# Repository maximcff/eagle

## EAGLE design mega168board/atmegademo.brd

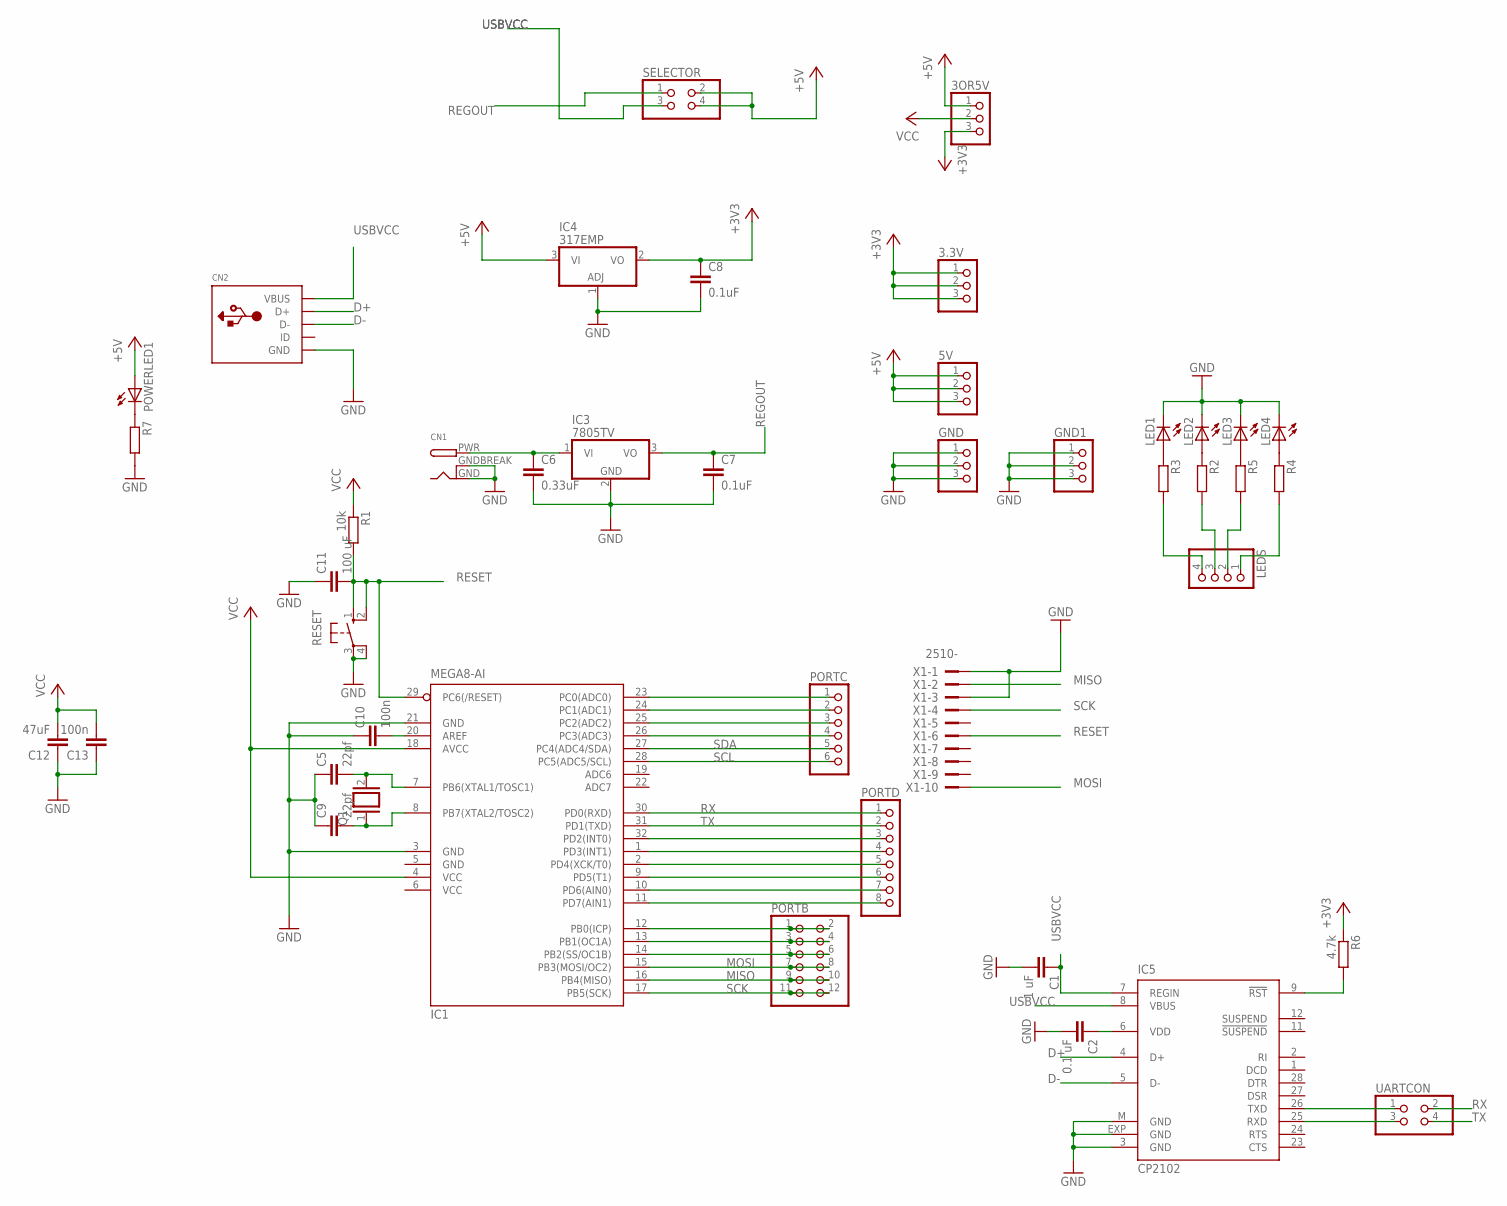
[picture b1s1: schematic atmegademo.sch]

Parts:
3.3V, 3OR5V, 5V: PINHD-1X3; 1X03
C1: 1 uF; C0805K
C2: 0.1 uF; C0805K
C5, C9: 22pf; C0805K
C6: 0.33uF; C0805K
C7, C8: 0.1uF; C0805K
C10, C13: 100n; C0805K
C11: 100 uF; C0805K
C12: 47uF; C0805K
CN1: DCBARRELPTH; DCJACK_2MM_PTH
CN2: USBMINIB; USB-MINIB
GND, GND1: PINHD-1X3; 1X03
IC1: MEGA8-AI; TQFP32-08
IC3: 7805TV; TO220V
IC4: 317EMP; SOT223
IC5: CP2102; MLP28
LED1, LED2, LED3, LED4: LEDCHIPLED_1206; CHIPLED_1206
LEDS: PINHD-1X4; 1X04
PORTB: PINHD-2X6; 2X06
PORTC: PINHD-1X6CLEAN; 1X06-CLEAN
PORTD: PINHD-1X8CLEANBIG; 1X08-CLEANBIG
POWERLED1: LEDCHIPLED_1206; CHIPLED_1206
Q1: XTAL/S; QS
R1: 10k; 0207/12
R2, R3, R4, R5, R7: R-EU_R0805; R0805
R6: 4.7k; R0805
RESET: 10-XX; B3F-10XX
SELECTOR: PINHD-2X2; 2X02
UARTCON: PINHD-2X2; 2X02
X1: 2510-; PAK100/2500-10

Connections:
+3V3: 3.3V.1, 3.3V.2, 3.3V.3, 3OR5V.3, C8.1, IC4.2 (VO), R6.1
+5V: 3OR5V.1, 5V.1, 5V.2, 5V.3, IC4.3 (VI), POWERLED1.A, SELECTOR.2, SELECTOR.4
D+: CN2.D+, IC5.4 (D+)
D-: CN2.D-, IC5.5 (D-)
GND: C1.2, C2.2, C5.1, C6.2, C7.2, C8.2, C9.1, C10.1, C11.1, C12.1, C13.1, CN1.GND, CN1.GNDBREAK, CN2.GND, GND.1, GND.2, GND.3, GND1.1, GND1.2, GND1.3, IC1.3 (GND), IC1.5 (GND), IC1.21 (GND), IC3.2 (GND), IC4.1 (ADJ), IC5.3 (GND), IC5.EXP (GND), IC5.M (GND), LED1.C, LED2.C, LED3.C, LED4.C, R7.2, RESET.3, RESET.4 (P1), X1.1, X1.3
MISO: IC1.16 (PB4(MISO)), PORTB.9, PORTB.10, X1.2
MOSI: IC1.15 (PB3(MOSI/OC2)), PORTB.7, PORTB.8, X1.10
unnamed: IC5.26 (TXD), UARTCON.1
unnamed: POWERLED1.C, R7.1
unnamed: C2.1, IC5.6 (VDD)
unnamed: IC5.9 (!RST), R6.2
unnamed: IC5.25 (RXD), UARTCON.3
unnamed: LEDS.4, R3.2
unnamed: LEDS.3, R2.2
unnamed: IC1.32 (PD2(INT0)), PORTD.3
unnamed: IC1.1 (PD3(INT1)), PORTD.4
unnamed: IC1.2 (PD4(XCK/T0)), PORTD.5
unnamed: C6.1, CN1.PWR, IC3.1 (VI)
unnamed: IC1.9 (PD5(T1)), PORTD.6
unnamed: IC1.23 (PC0(ADC0)), PORTC.1
unnamed: IC1.10 (PD6(AIN0)), PORTD.7
unnamed: IC1.11 (PD7(AIN1)), PORTD.8
unnamed: IC1.24 (PC1(ADC1)), PORTC.2
unnamed: IC1.25 (PC2(ADC2)), PORTC.3
unnamed: IC1.26 (PC3(ADC3)), PORTC.4
unnamed: LEDS.2, R5.2
unnamed: LED1.A, R3.1
unnamed: LED2.A, R2.1
unnamed: C10.2, IC1.20 (AREF)
unnamed: C5.2, IC1.7 (PB6(XTAL1/TOSC1)), Q1.2
unnamed: LED4.A, R4.1
unnamed: LED3.A, R5.1
unnamed: C9.2, IC1.8 (PB7(XTAL2/TOSC2)), Q1.1
unnamed: IC1.13 (PB1(OC1A)), PORTB.3, PORTB.4
unnamed: IC1.14 (PB2(SS/OC1B)), PORTB.5, PORTB.6
unnamed: IC1.12 (PB0(ICP)), PORTB.1, PORTB.2
unnamed: LEDS.1, R4.2
REGOUT: C7.1, IC3.3 (VO), SELECTOR.1
RESET: C11.2, IC1.29 (PC6(/RESET)), R1.2, RESET.1 (S), RESET.2 (S1), X1.6
RX: IC1.30 (PD0(RXD)), PORTD.1, UARTCON.2
SCK: IC1.17 (PB5(SCK)), PORTB.11, PORTB.12, X1.4
SCL: IC1.28 (PC5(ADC5/SCL)), PORTC.6
SDA: IC1.27 (PC4(ADC4/SDA)), PORTC.5
TX: IC1.31 (PD1(TXD)), PORTD.2, UARTCON.4
USBVCC: C1.1, CN2.VBUS, IC5.7 (REGIN), IC5.8 (VBUS), SELECTOR.3
VCC: 3OR5V.2, C12.2, C13.2, IC1.4 (VCC), IC1.6 (VCC), IC1.18 (AVCC), R1.1

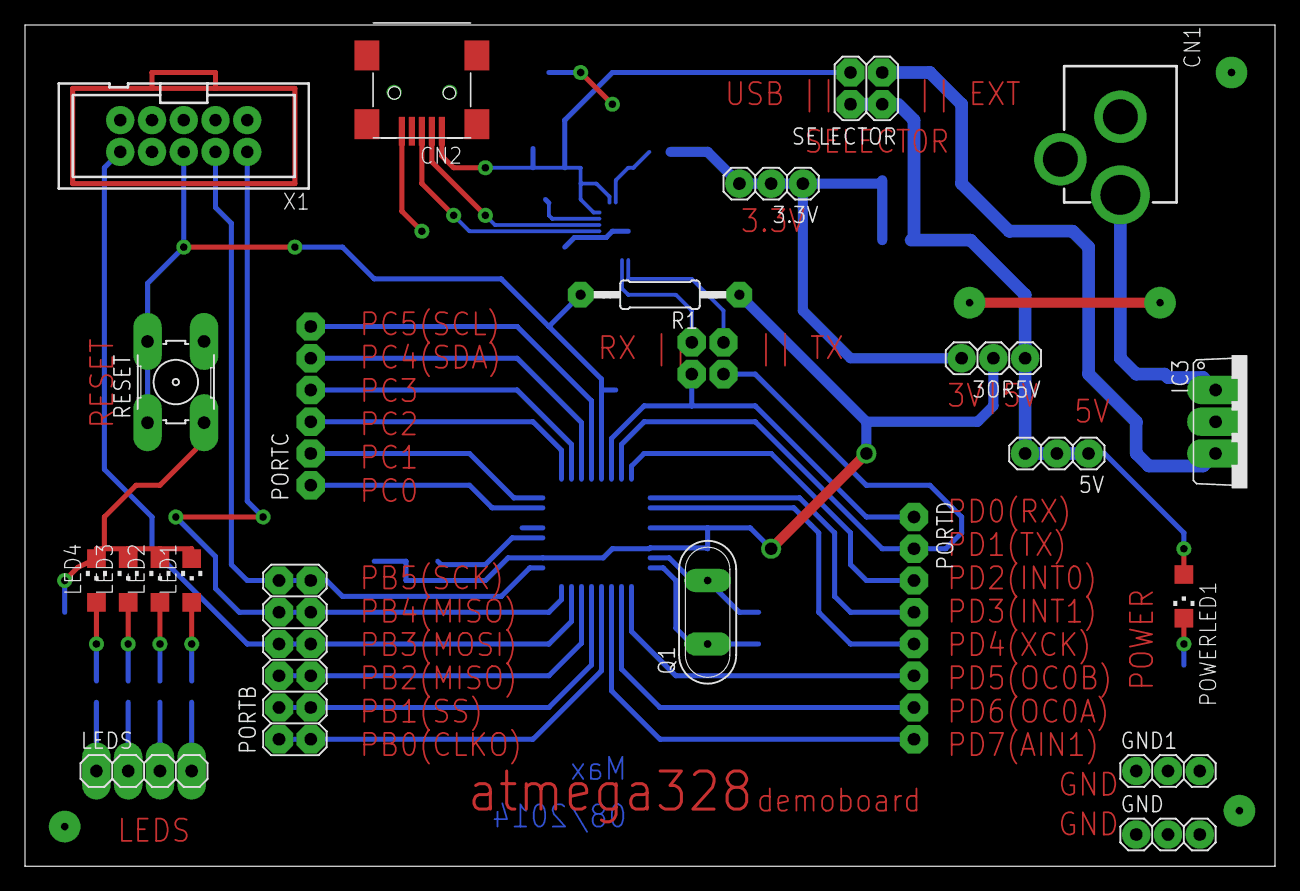
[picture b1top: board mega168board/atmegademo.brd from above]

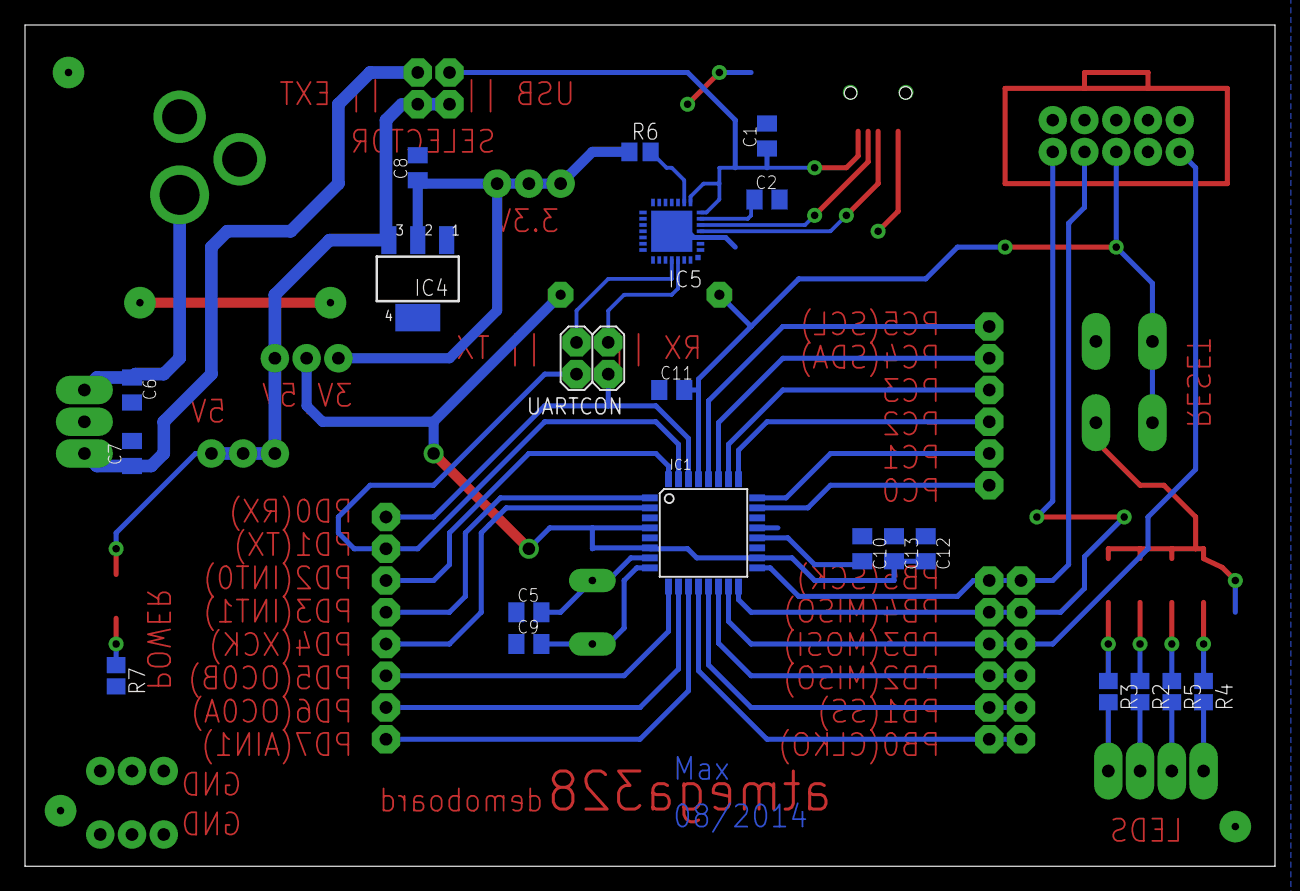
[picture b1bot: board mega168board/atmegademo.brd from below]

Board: 2 copper layers, 100.0 x 67.3 mm, 43 parts (21 on the bottom side), 46 nets.

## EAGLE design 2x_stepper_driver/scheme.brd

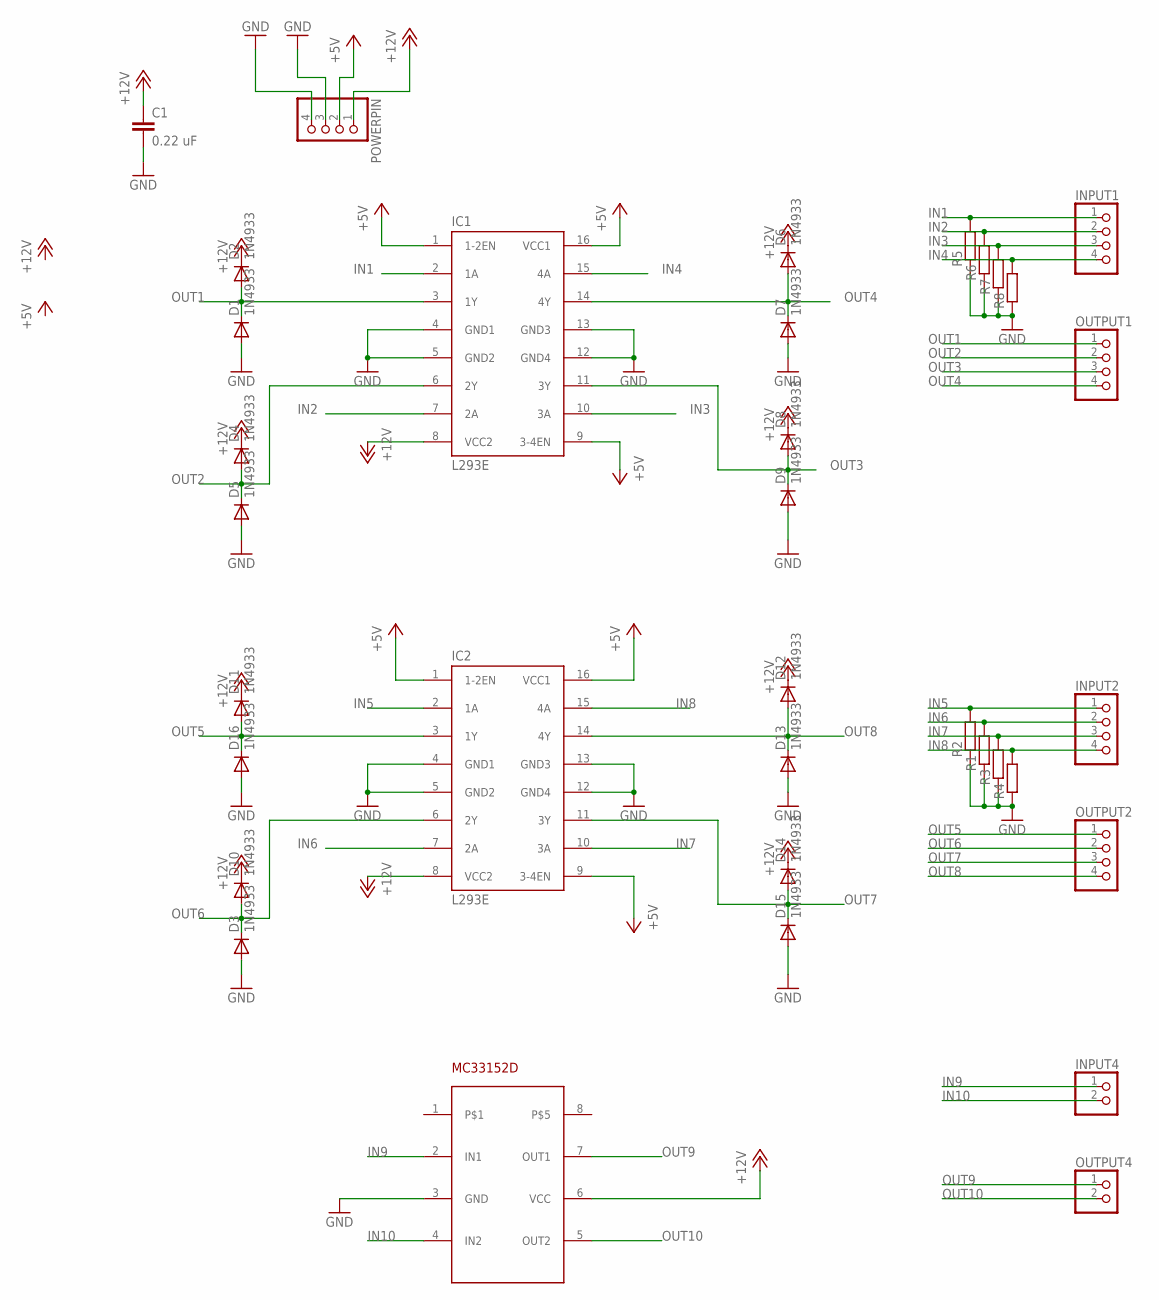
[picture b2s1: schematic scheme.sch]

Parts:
C1: 0.22 uF; C0805K
D1, D2, D3, D4, D5, D6, D7, D8, D9, D10, D11, D12, D13, D14, D15, D16: 1N4933; DO41-10
IC1, IC2: L293E; DIL16
INPUT1, INPUT2: PINHD-1X4; 1X04
INPUT4: PINHD-1X2; 1X02
MC33152D: MC33152D; SOIC8
OUTPUT1, OUTPUT2: PINHD-1X4; 1X04
OUTPUT4: PINHD-1X2; 1X02
POWERPIN: PINHD-1X4; 1X04
R1, R2, R3, R4, R5, R6, R7, R8: R-EU_R0805; R0805

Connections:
+5V: IC1.1 (1-2EN), IC1.9 (3-4EN), IC1.16 (VCC1), IC2.1 (1-2EN), IC2.9 (3-4EN), IC2.16 (VCC1), POWERPIN.2
+12V: C1.1, D2.C, D4.C, D6.C, D8.C, D10.C, D11.C, D12.C, D14.C, IC1.8 (VCC2), IC2.8 (VCC2), MC33152D.6 (VCC), POWERPIN.1
GND: C1.2, D1.A, D3.A, D5.A, D7.A, D9.A, D13.A, D15.A, D16.A, IC1.4 (GND1), IC1.5 (GND2), IC1.12 (GND4), IC1.13 (GND3), IC2.4 (GND1), IC2.5 (GND2), IC2.12 (GND4), IC2.13 (GND3), MC33152D.3 (GND), POWERPIN.3, POWERPIN.4, R1.1, R2.1, R3.1, R4.1, R5.1, R6.1, R7.1, R8.1
IN1: IC1.2 (1A), INPUT1.1, R5.2
IN2: IC1.7 (2A), INPUT1.2, R6.2
IN3: IC1.10 (3A), INPUT1.3, R7.2
IN4: IC1.15 (4A), INPUT1.4, R8.2
IN5: IC2.2 (1A), INPUT2.1, R2.2
IN6: IC2.7 (2A), INPUT2.2, R1.2
IN7: IC2.10 (3A), INPUT2.3, R3.2
IN8: IC2.15 (4A), INPUT2.4, R4.2
IN9: INPUT4.1, MC33152D.2 (IN1)
IN10: INPUT4.2, MC33152D.4 (IN2)
OUT1: D1.C, D2.A, IC1.3 (1Y), OUTPUT1.1
OUT2: D4.A, D5.C, IC1.6 (2Y), OUTPUT1.2
OUT3: D8.A, D9.C, IC1.11 (3Y), OUTPUT1.3
OUT4: D6.A, D7.C, IC1.14 (4Y), OUTPUT1.4
OUT5: D11.A, D16.C, IC2.3 (1Y), OUTPUT2.1
OUT6: D3.C, D10.A, IC2.6 (2Y), OUTPUT2.2
OUT7: D14.A, D15.C, IC2.11 (3Y), OUTPUT2.3
OUT8: D12.A, D13.C, IC2.14 (4Y), OUTPUT2.4
OUT9: MC33152D.7 (OUT1), OUTPUT4.1
OUT10: MC33152D.5 (OUT2), OUTPUT4.2

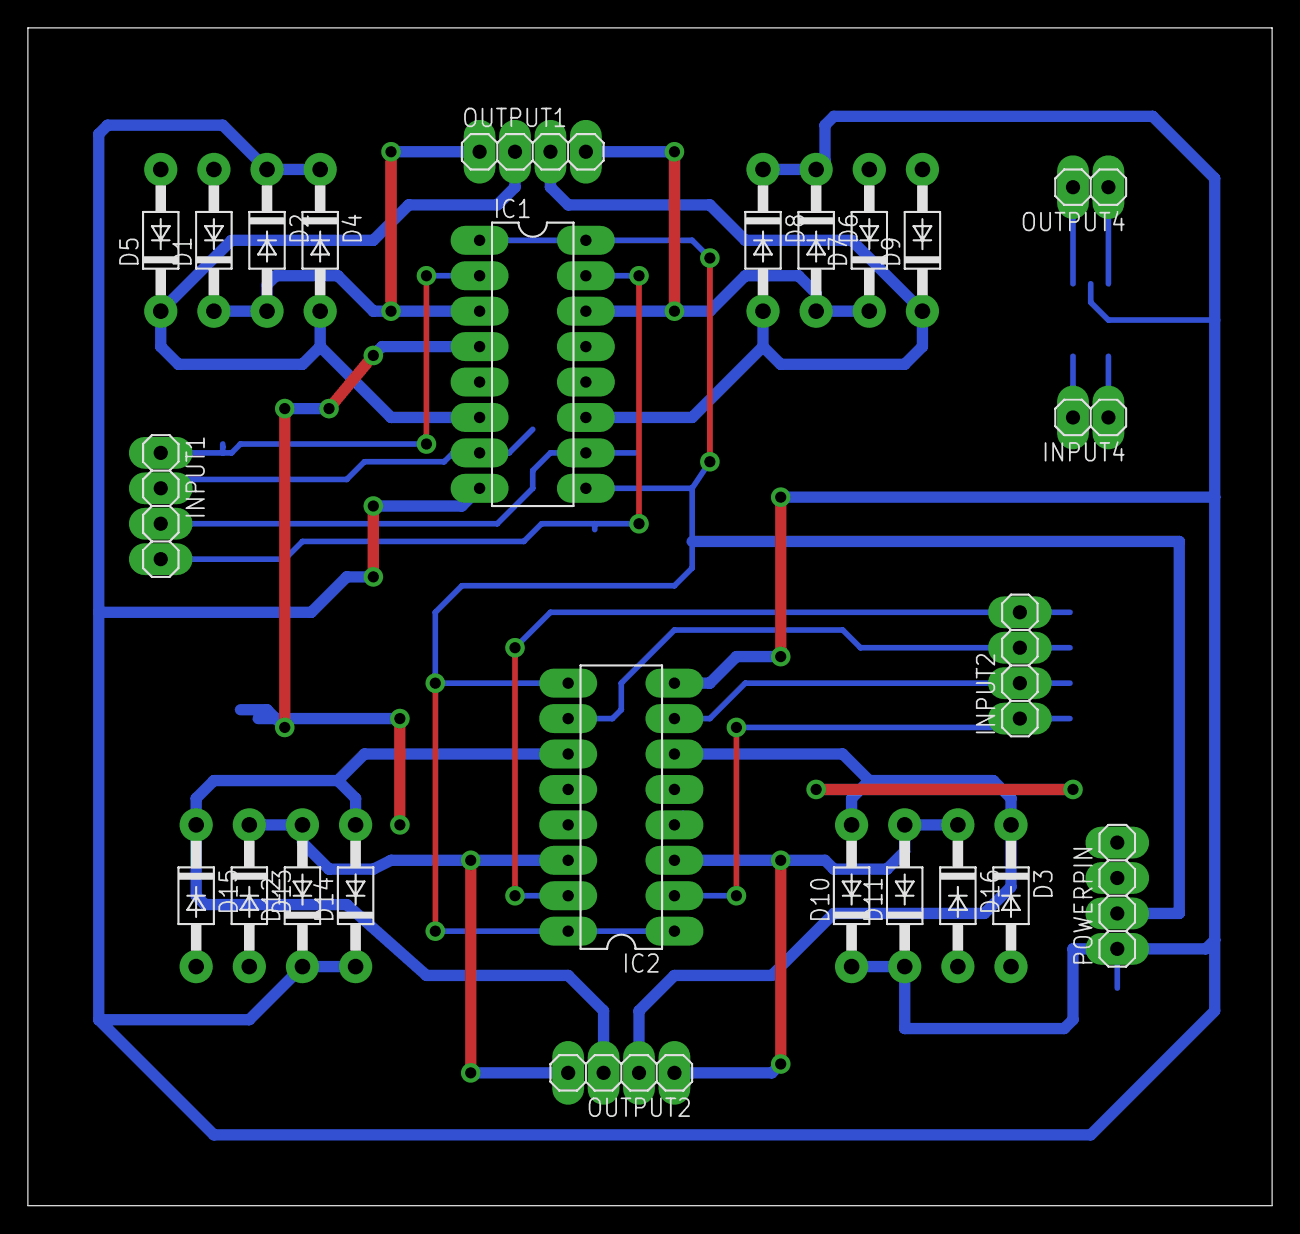
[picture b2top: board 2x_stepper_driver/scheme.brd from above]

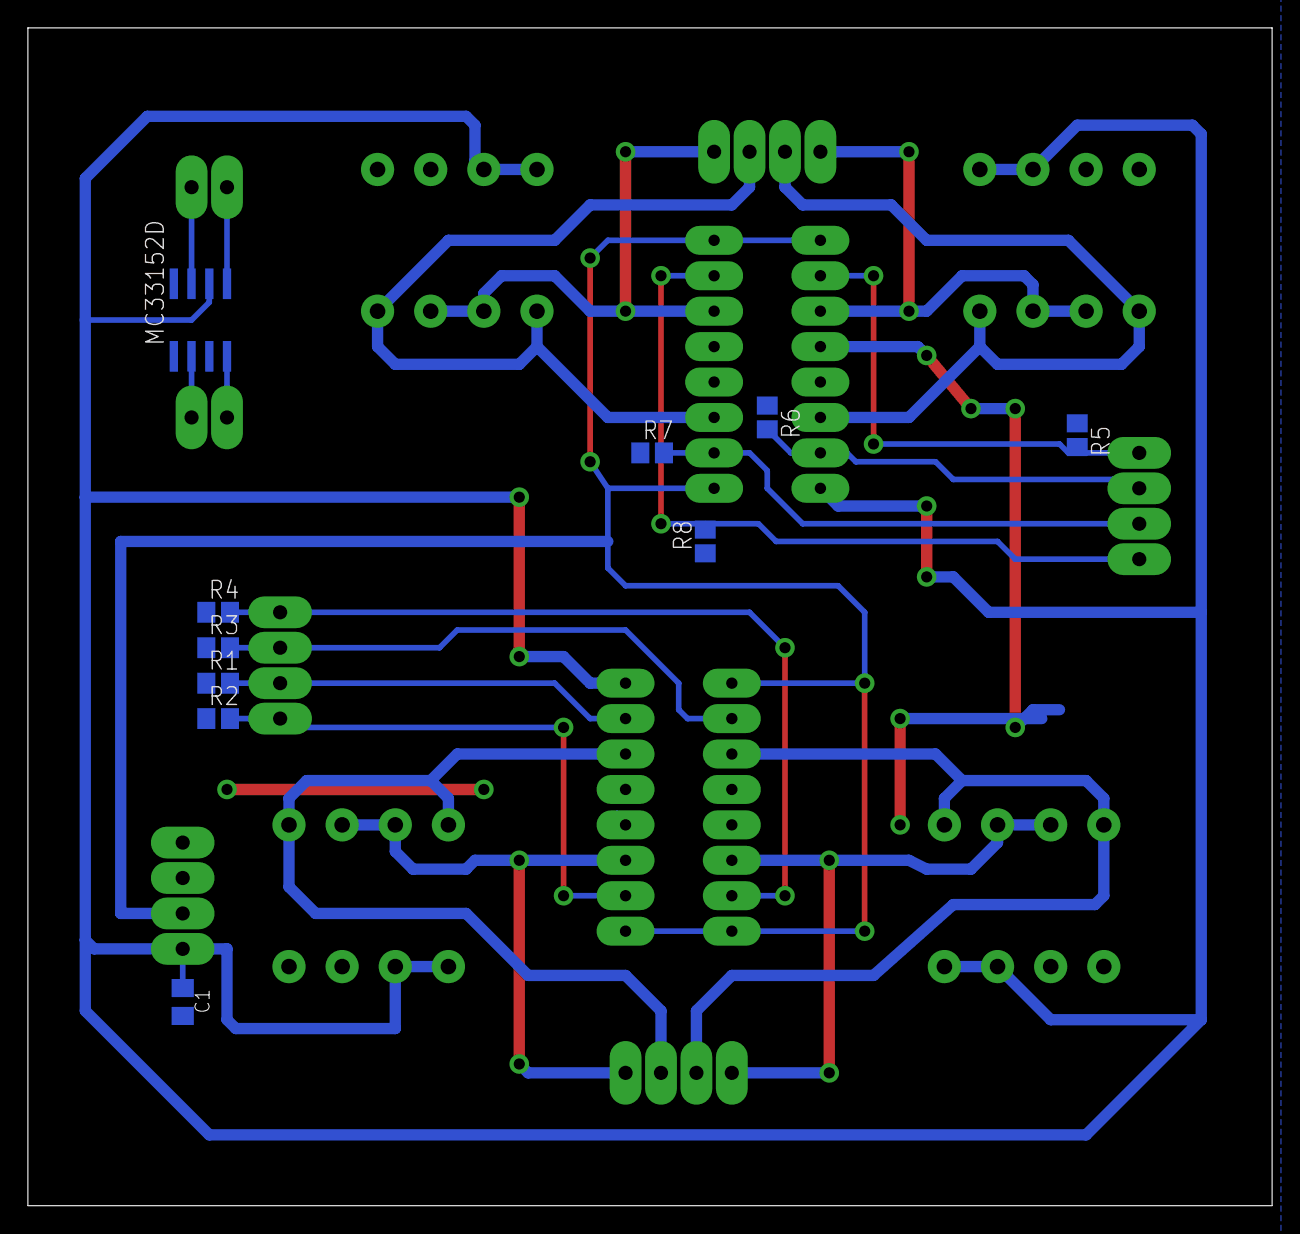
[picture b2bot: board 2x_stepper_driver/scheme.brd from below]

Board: 2 copper layers, 89.2 x 84.4 mm, 35 parts (10 on the bottom side), 23 nets.

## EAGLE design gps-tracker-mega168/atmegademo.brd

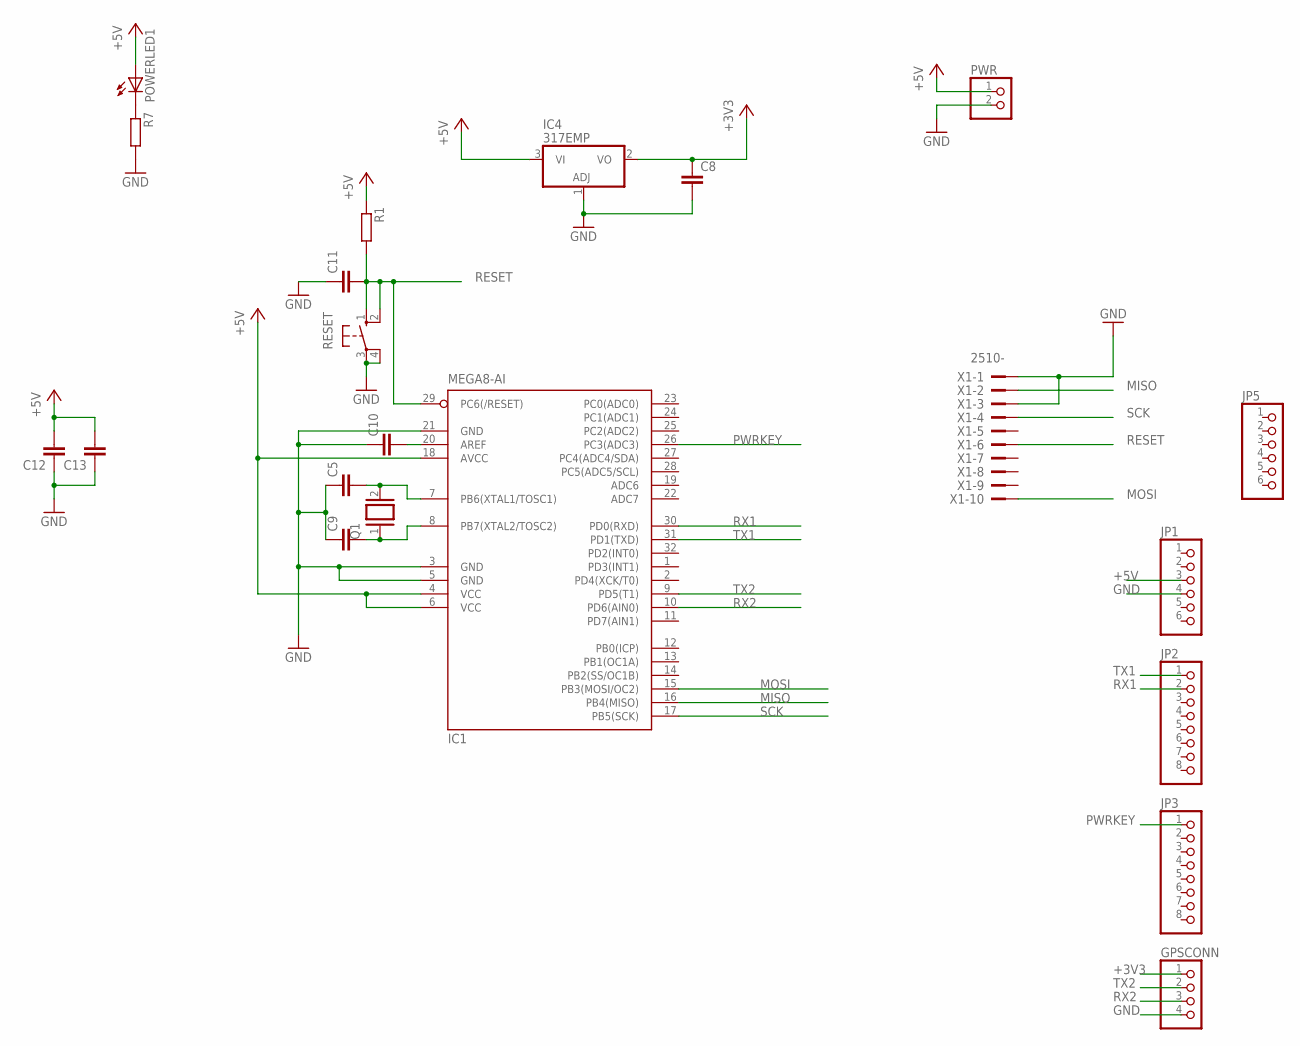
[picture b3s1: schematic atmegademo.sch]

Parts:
C5, C8, C9, C10, C11, C12, C13: C-EUC0805K; C0805K
GPSCONN: PINHD-1X4; 1X04
IC1: MEGA8-AI; TQFP32-08
IC4: 317EMP; SOT223
JP1, JP5: PINHD-1X6CLEAN; 1X06-CLEAN
JP2, JP3: PINHD-1X8CLEANBIG; 1X08-CLEANBIG
POWERLED1: LEDCHIP-LED0805; CHIP-LED0805
PWR: PINHD-1X2; 1X02
Q1: XTAL/S; QS
R1, R7: R-EU_R0805; R0805
RESET: 10-XX; B3F-10XX
X1: 2510-; PAK100/2500-10

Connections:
+3V3: C8.1, GPSCONN.1, IC4.2 (VO)
+5V: C12.2, C13.2, IC1.4 (VCC), IC1.6 (VCC), IC1.18 (AVCC), IC4.3 (VI), JP1.3, POWERLED1.A, PWR.1, R1.1
GND: C5.1, C8.2, C9.1, C10.1, C11.1, C12.1, C13.1, GPSCONN.4, IC1.3 (GND), IC1.5 (GND), IC1.21 (GND), IC4.1 (ADJ), JP1.4, PWR.2, R7.2, RESET.3, RESET.4 (P1), X1.1, X1.3
MISO: IC1.16 (PB4(MISO)), X1.2
MOSI: IC1.15 (PB3(MOSI/OC2)), X1.10
unnamed: POWERLED1.C, R7.1
unnamed: C10.2, IC1.20 (AREF)
unnamed: C5.2, IC1.7 (PB6(XTAL1/TOSC1)), Q1.2
unnamed: C9.2, IC1.8 (PB7(XTAL2/TOSC2)), Q1.1
PWRKEY: IC1.26 (PC3(ADC3)), JP3.1
RESET: C11.2, IC1.29 (PC6(/RESET)), R1.2, RESET.1 (S), RESET.2 (S1), X1.6
RX1: IC1.30 (PD0(RXD)), JP2.2
RX2: GPSCONN.3, IC1.10 (PD6(AIN0))
SCK: IC1.17 (PB5(SCK)), X1.4
TX1: IC1.31 (PD1(TXD)), JP2.1
TX2: GPSCONN.2, IC1.9 (PD5(T1))

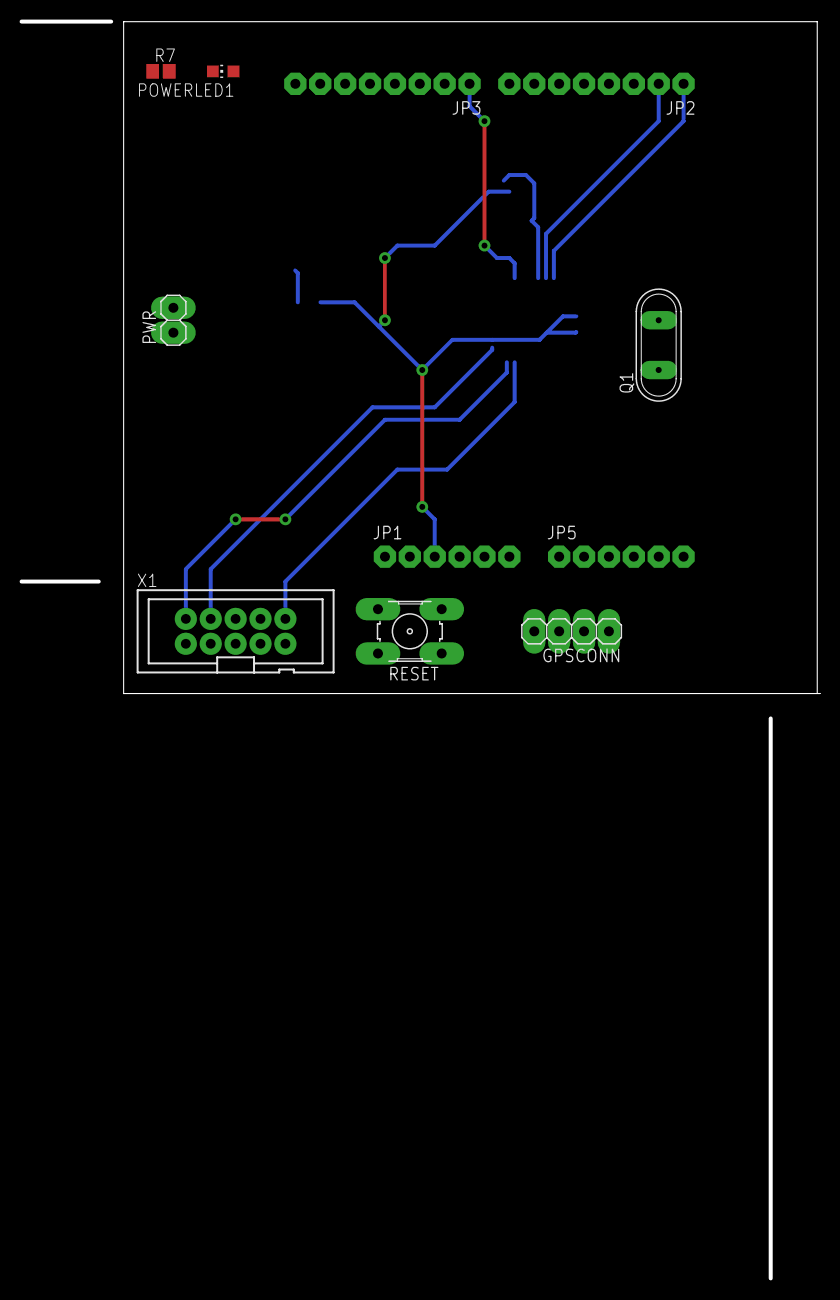
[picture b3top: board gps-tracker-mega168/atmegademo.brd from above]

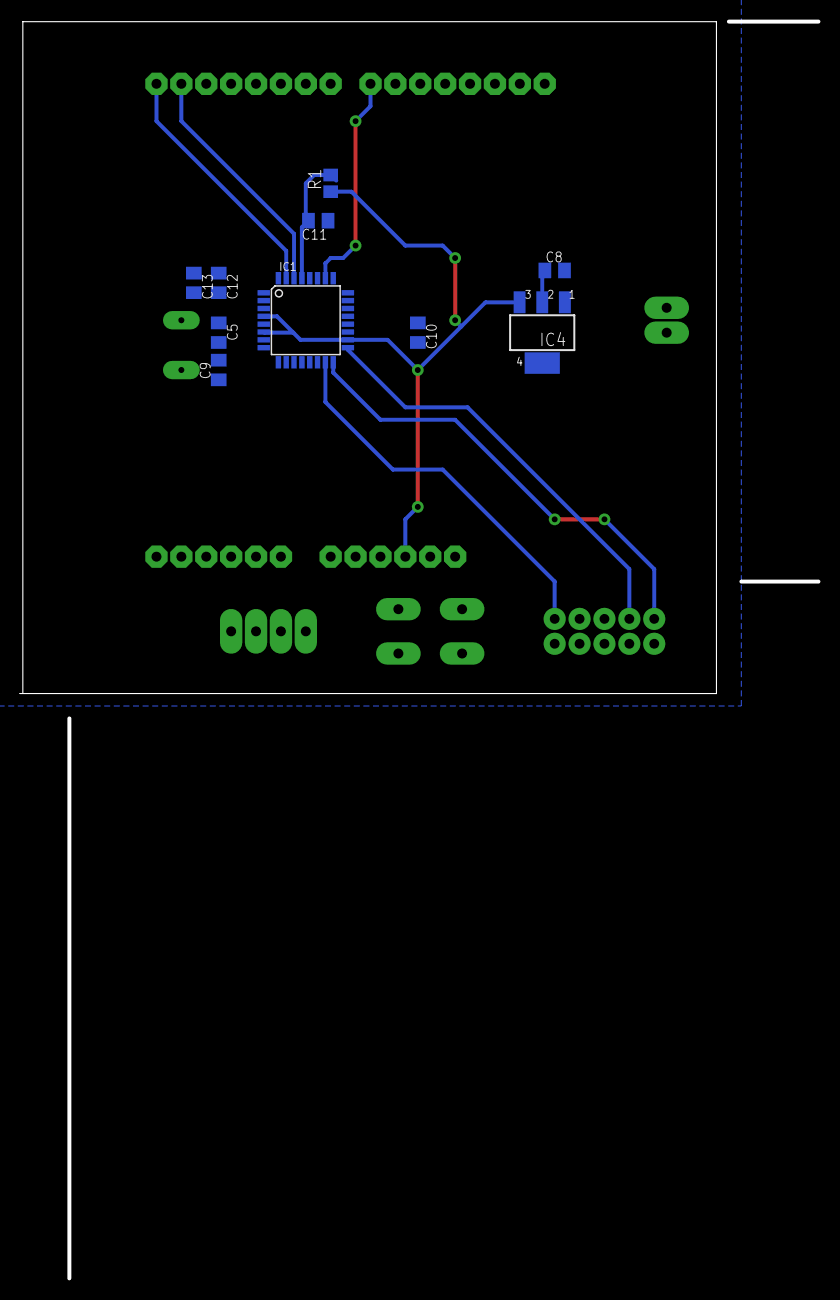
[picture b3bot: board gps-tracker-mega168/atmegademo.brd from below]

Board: 2 copper layers, 81.5 x 128.3 mm, 21 parts (10 on the bottom side), 16 nets.

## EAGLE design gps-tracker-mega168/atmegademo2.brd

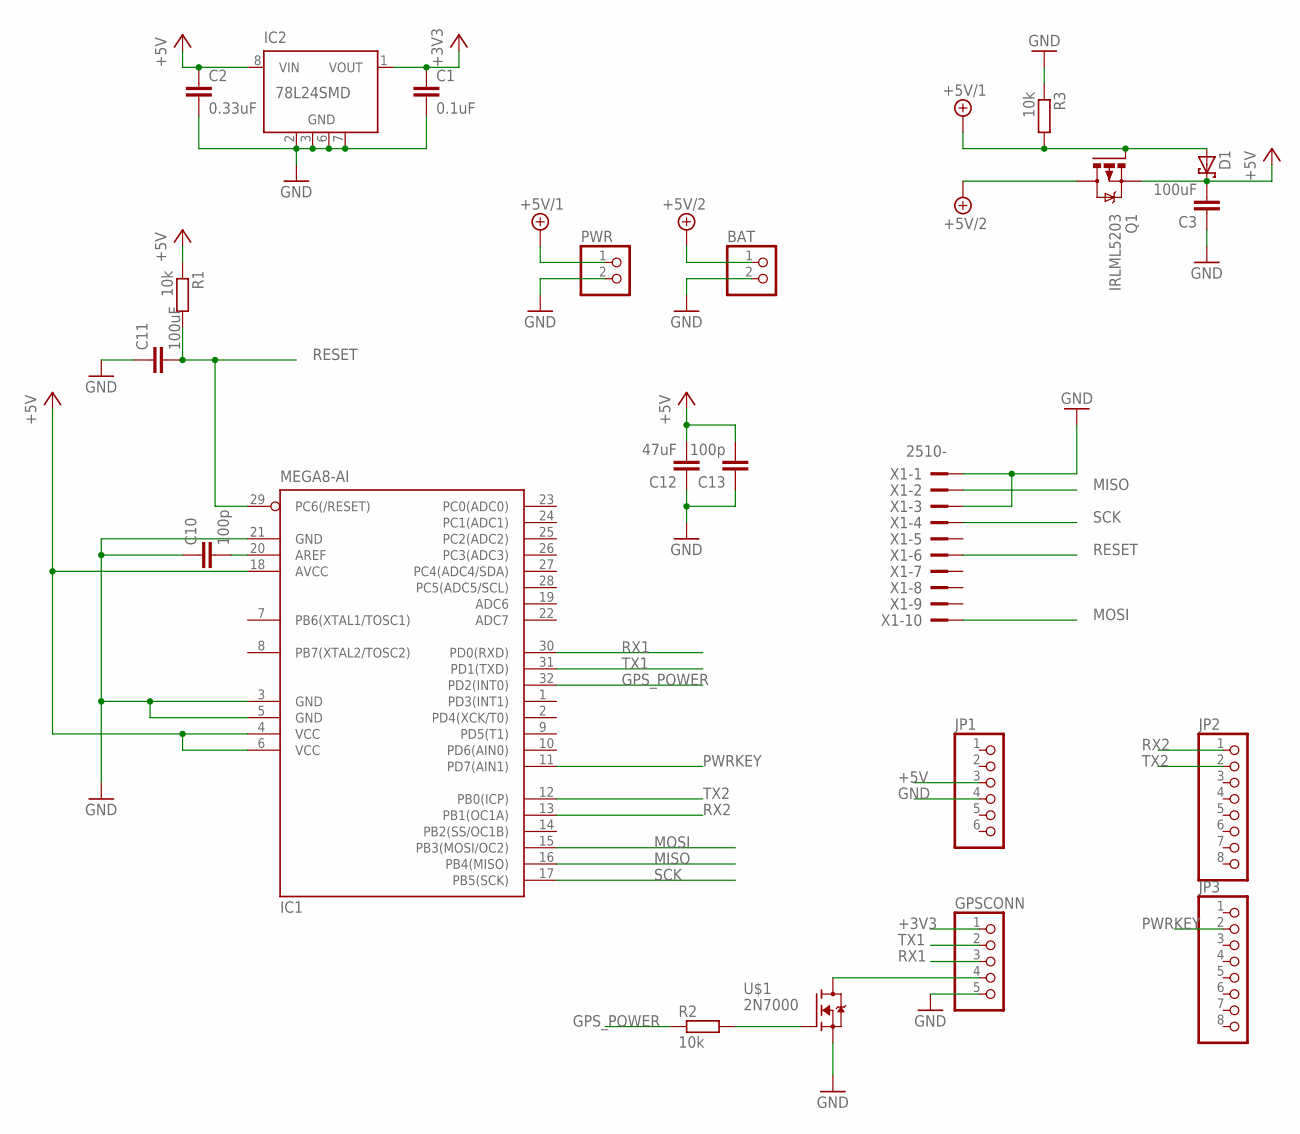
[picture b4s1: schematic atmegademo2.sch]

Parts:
BAT: PINHD-1X2; 1X02
C1: 0.1uF; C0805K
C2: 0.33uF; C0805K
C3, C11: 100uF; C0805K
C10, C13: 100p; C0805K
C12: 47uF; C0805K
D1: SCHOTTKY-DIODESMD; SMB
GPSCONN: PINHD-1X5; 1X05
IC1: MEGA8-AI; TQFP32-08
IC2: 78L24SMD; SO08
JP1: PINHD-1X6CLEAN; 1X06-CLEAN
JP2, JP3: PINHD-1X8CLEANBIG; 1X08-CLEANBIG
PWR: PINHD-1X2; 1X02
Q1: IRLML5203; MICRO3
R1, R2, R3: 10k; R0805
U$1: 2N7000; TO92-
X1: 2510-; PAK100/2500-10

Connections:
+3V3: C1.1, GPSCONN.1, IC2.1 (VOUT)
+5V: C2.1, C3.2, C12.2, C13.2, D1.C, IC1.4 (VCC), IC1.6 (VCC), IC1.18 (AVCC), IC2.8 (VIN), JP1.3, Q1.2 (S), R1.1
+5V/1: D1.A, PWR.1, Q1.1 (G), R3.2
+5V/2: BAT.1, Q1.3 (D)
GND: BAT.2, C1.2, C2.2, C3.1, C10.1, C11.1, C12.1, C13.1, GPSCONN.5, IC1.3 (GND), IC1.5 (GND), IC1.21 (GND), IC2.2 (GND), IC2.3 (GND), IC2.6 (GND), IC2.7 (GND), JP1.4, PWR.2, R3.1, U$1.3 (S), X1.1, X1.3
GPS_POWER: IC1.32 (PD2(INT0)), R2.1
MISO: IC1.16 (PB4(MISO)), X1.2
MOSI: IC1.15 (PB3(MOSI/OC2)), X1.10
unnamed: GPSCONN.4, U$1.1 (D)
unnamed: R2.2, U$1.2 (G)
unnamed: C10.2, IC1.20 (AREF)
PWRKEY: IC1.11 (PD7(AIN1)), JP3.2
RESET: C11.2, IC1.29 (PC6(/RESET)), R1.2, X1.6
RX1: GPSCONN.3, IC1.30 (PD0(RXD))
RX2: IC1.13 (PB1(OC1A)), JP2.1
SCK: IC1.17 (PB5(SCK)), X1.4
TX1: GPSCONN.2, IC1.31 (PD1(TXD))
TX2: IC1.12 (PB0(ICP)), JP2.2

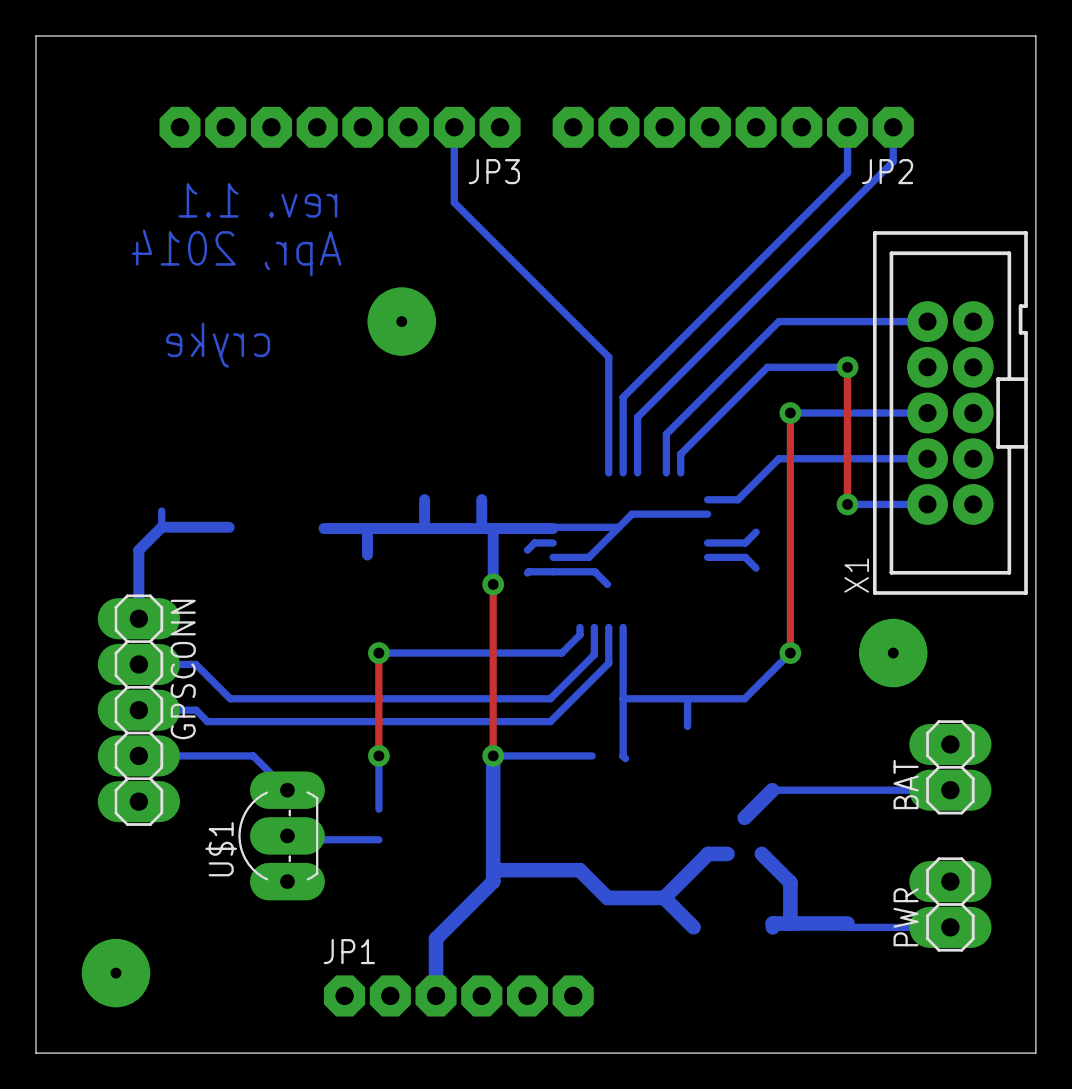
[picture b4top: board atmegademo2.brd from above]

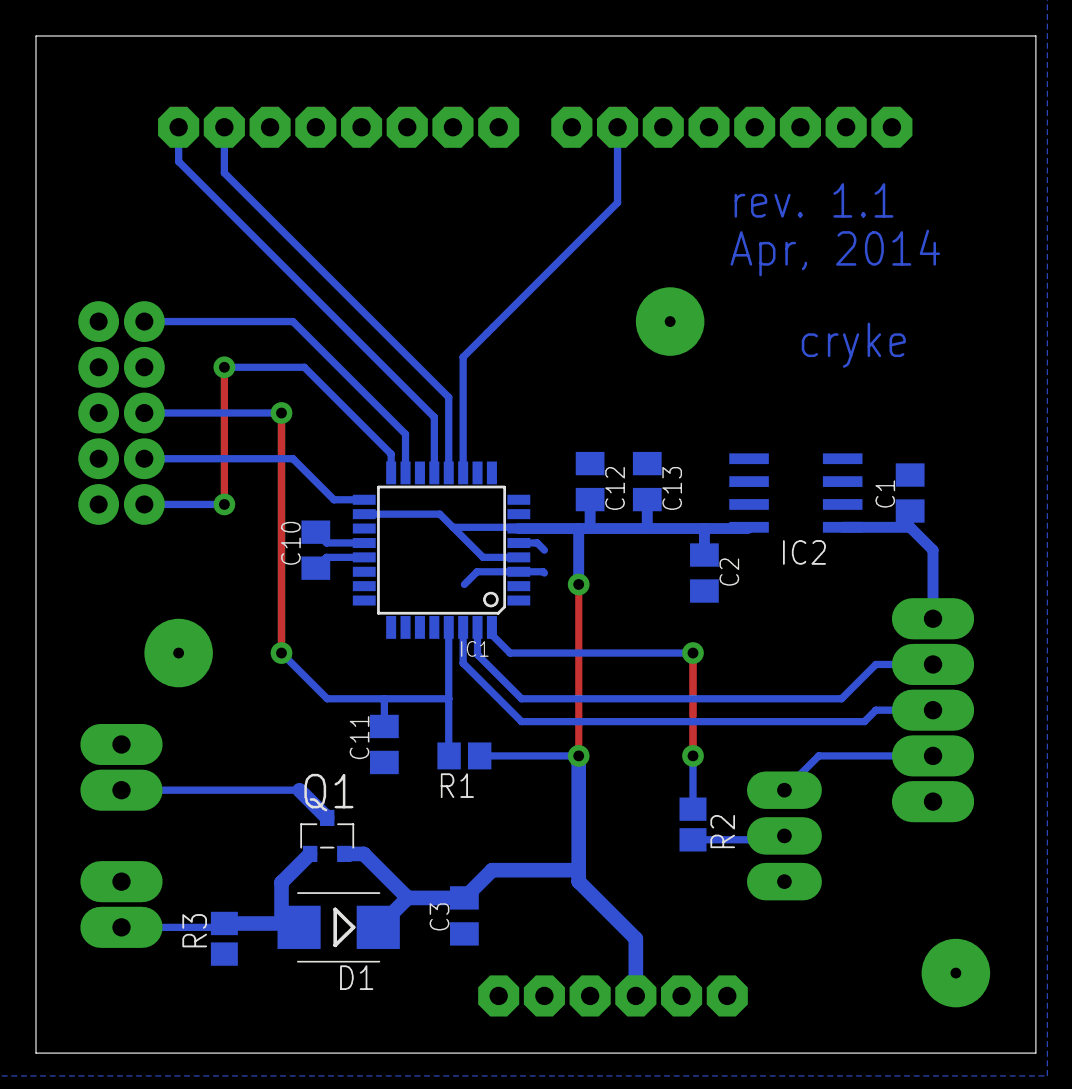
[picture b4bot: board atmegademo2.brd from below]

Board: 2 copper layers, 55.6 x 56.5 mm, 22 parts (14 on the bottom side), 18 nets.

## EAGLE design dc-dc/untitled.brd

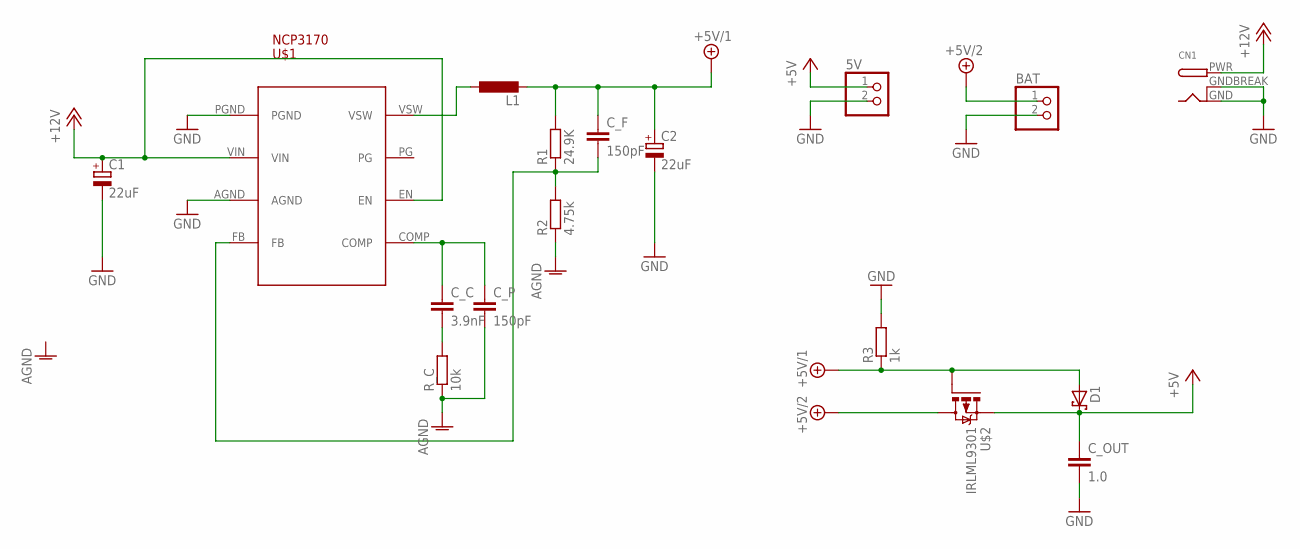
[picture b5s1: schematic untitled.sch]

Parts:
5V: PINHD-1X2; 1X02
BAT: PINHD-1X2; 1X02
C1, C2: 22uF; E2-5
CN1: DCBARRELPTH; DCJACK_2MM_PTH
C_C: 3.9nF; C0805K
C_F: 150pF; C0805K
C_OUT: 1.0; C0805K
C_P: 150pF; C0805K
D1: SCHOTTKY-DIODESMD; SMB
L1: L-EU0207/7; 0207/7
R1: 24.9K; R0805
R2: 4.75k; R0805
R3: 1k; R0805
R_C: 10k; R0805
U$1: NCP3170; SOIC8
U$2: IRLML9301; SOT23

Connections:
+5V: 5V.1, C_OUT.1, D1.C, U$2.S
+5V/1: C2.+, C_F.1, D1.A, L1.2, R1.2, R3.1, U$2.G
+5V/2: BAT.1, U$2.D
+12V: C1.+, CN1.PWR, U$1.EN, U$1.VIN
AGND: C_P.2, R2.1, R_C.1
GND: 5V.2, BAT.2, C1.-, C2.-, CN1.GND, CN1.GNDBREAK, C_OUT.2, R3.2, U$1.AGND, U$1.PGND
unnamed: C_C.1, C_P.1, U$1.COMP
unnamed: C_C.2, R_C.2
unnamed: C_F.2, R1.1, R2.2, U$1.FB
unnamed: L1.1, U$1.VSW

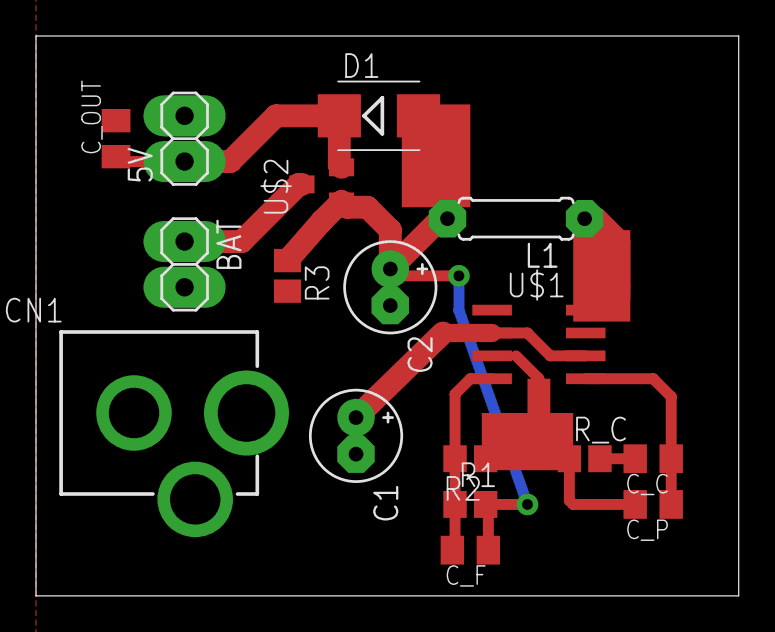
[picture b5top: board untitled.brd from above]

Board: 2 copper layers, 39.0 x 31.1 mm, 17 parts (0 on the bottom side), 10 nets.
